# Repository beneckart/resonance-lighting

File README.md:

# Resonance Lighting

Power and lighting workstream for the **Resonance Tree** -- a bamboo art installation for Burning Man 2026 + 2027. This repo covers the roughly 130 solar/battery-powered, mesh-networked lighting fixtures in and around the tree -- four classes: hanging downlights, perimeter lights, trunk lights, and the central chandelier (canonical counts: the fleet table in `docs/block-diagram/SYSTEM.md`; current allocation: ADR 0032).

Sister tracks (not in this repo): bamboo structure (Bamboo Pure, Bali), structural engineering (Ed), parametric lighting design (Vishnu), project management (Elliot + Co-Work agent).

## Post-event storage and 2027 planning

Start with the [2026 postmortem and future-work index](docs/postmortem/README.md)
for the container-storage outcome, Oakland inventory, PROTECT investigation and
2027 hardware/tooling brainstorming. The
[storage and wake guide](docs/howto/FIXTURE_STORAGE_AND_WAKE.md) documents the
implemented USB/solar-wake ship mode, RESET-wake sleep, date picker and exact
retained firmware. These records supersede pre-event status where noted; the
2027 concepts remain discussion drafts.

## Who's working here

- **Ben Eckart** -- power systems, firmware, mesh networking. Owns `/firmware/` and `/hardware/`.
- **Steve Eckart** -- enclosure design, 3D printing, mechanical fit. Owns `/enclosure/`.

Both work with AI pair-programmers. Coordinate via `LOG.md`, `TODO.md`, and ADRs.
Firmware builders additionally use
[`docs/howto/FIRMWARE_ARTIFACT_HANDOFF.md`](docs/howto/FIRMWARE_ARTIFACT_HANDOFF.md)
so separate benches do not reuse revisions or silently flash each other's targets.

## What is the deliverable

Nominally 130 modular lighting fixtures in four classes -- 72 hanging downlights
in three rings of 24, 24 all-HEX perimeter lights on shepherd hooks, about 16 trunk
lights trending RGBW, and 18 mixed HEX/RGBW chandelier lights. The team intends to
build this full layout; fewer fixtures are a contingency for an unforeseen issue.
The archetype (hanging downlight) is:

- A bamboo lantern body, fabricated by Bamboo Pure in Bali.
- A solar "hat" enclosure that sits partially inside, partially over the bamboo top.
- A solar panel, rechargeable battery, controller board, LED module, sensors
  (accelerometer + downward ToF), and a 3D-printed patterned aperture / gobo.
- Firmware that supports autonomous ambient lighting, ESP-NOW state exchange, standard OTA maintenance updates, telemetry, and graceful low-power behavior.

The other classes are variants on the same electronics: perimeter lights use HEX and
face the ToF outward; trunk lights drop the gobo and are moving toward all RGBW while
a smaller lensed 3 W RGB module is tested for extra throw; chandelier lights live in
a carpenter-built box, likely on 6 Ah cells with USB-C top-ups. All share one firmware
image.

Steve's NeoHex Magic Wand is a separate one-off fleet peer, not a fifth
production class. Its PowerFeather identity is permanently `F40344` /
`68:EE:8F:F4:03:44`, its registry role is `magic_wand`, and batch OTA tooling
requires a dedicated single-target acknowledgement before it will touch that
MAC (ADR 0050). See `docs/projects/NeoHex-Magic-Wand/README.md`.

## Current architecture direction

**PowerFeather V2 (ESP32-S3) is the confirmed reference** for the controller / solar-and-battery manager / telemetry, after 5-board feasibility testing (ADR 0021): ESP-NOW mesh at scale, battery-only no-touch OTA + A/B rollback, and the solar charge path are all validated on hardware. Chemistry is **LiFePO4** (ADR 0002); batteries are two-tier since 2026-07-24 (ADR 0025): 33140 15 Ah in the large hats (downlights; qualification pending) and the fullbattery 32700 6 Ah, qualified n=2, in the small hats.

**The production path is decided: COTS PowerFeather V2, with a nominal 130-fixture
deployment (ADRs 0024 and 0032).**
158 boards are bought (68 received + 90 ordered 2026-07-09; ledger: `ops/PROCUREMENT.md`).
The custom PowerFeather-derived PCBA (ESP32-S3-WROOM module, BQ25628E-class charger,
MAX17260-class gauge, buck-boost 3.3 V rail, switchable rails, keyed connectors) is
the 2027 option, carrying the ADR 0028 bus-integrity rules.

The **LED axis is a mixed fleet by optical role** (ADR 0022): SK6812 "HEX"
direct-GPIO for close-range animation / ambient glow, and a 4 W RGBW point source for
long-throw crisp gobo projection. Both are driven **direct-GPIO off a free pin**, both
fed from the switchable 3V3 rail -- decided by instrumented A/B through
production-realistic cabling (ADR 0029 + 2026-07-11 amendment); the 4.2 V boost is
measured and shelved. The type mix by class is in the
SYSTEM.md fleet table (tentative until installation). The earlier Adafruit
IS31FL3741 13x9 STEMMA-QT matrix was **ruled out** (ADR 0018) -- it browns out the
board on battery under WiFi (shared charger/gauge I2C bus). The earlier COTS bake-off
candidates (FeatherS2 Neo, Atom Matrix, NeoHEX, DFR0559) served their purpose;
PowerFeather V2 won.

**Sensors and class identity** (ADRs 0027, 0034, 0041, 0067): every downlight
carries an MSA311 accelerometer + downward TMF8820-mini multizone ToF; perimeter
lights carry an outward VL53L5CX; trunk/uplights normally carry only MSA311;
chandelier lights carry no class sensors. Auto-classification is ordered ToF then
MSA311 at `0x62`, with a sensorless uplight fallback for the already-installed
2026 fleet. Remembered downlight/perimeter classes survive a missing ToF. Future
chandelier PowerFeathers are rostered by exact MAC and persist `class_ovr=4`
before installation. BMP581 is non-classifying environmental telemetry on the
outer 24 downlights. Fused IMUs were rejected (per-device calibration does not
scale to the fleet). The **noisemaker**
is decided (ADR 0030/0071): a solenoid mallet physically strikes an installed
finger cymbal on each canopy bamboo assembly -- daytime
solar-surplus percussion; the speaker-synth path was abandoned once the strikes
proved out.

**Production show timing is scheduled** (ADR 0031): four purchased SAM-M8Q modules
are the initial GPS/GNSS soft anchors for absolute UTC, and four purchased Adafruit
DS3231 modules are the initial battery-backed RTC holdover anchors. ESP-NOW distributes
time quality to the rest of the fleet, so all roughly 130 fixtures do not need RTCs.
Panel/lux dusk inference remains useful bench telemetry but is not the production show
clock.

**Performance audio has a dedicated optional publisher** (ADR 0035): a received
PUCA DSP Original Edition in its Eurorack expansion, paired with a RODE VideoMic
NTG, will analyze one clean audio source and publish directed show frames over
ESP-NOW. The already-proven CoreS3 + Module Audio path remains the independent
fallback. PUCA hardware is on hand; its development firmware now passes the
powered-Pod20 codec/stereo/control/radio/full-census baseline with locked
standalone HEARTBEAT startup. The performer's exact waveform, visible fixture
fidelity/fallback, and field validation remain pending. See
`hardware/puca-audio-bridge/README.md`.

**The camp network is pinned to the mesh channel** (ADR 0036). The ESP32-S3 has
one 2.4 GHz radio, so WiFi STA and ESP-NOW must share a channel, and in STA mode
the access point picks it. Every bridge so far dodges this by staying
unassociated; any device that wants the mesh and the internet at once cannot.
The camp AP (Starlink in bypass mode -> GL.iNet Beryl AX) therefore serves a
dedicated 2.4 GHz SSID fixed to channel 11, and any device that associates while
using ESP-NOW must verify the channel and drop WiFi rather than lose the mesh.
Router ordered, not yet configured; runbook in `docs/howto/CAMP_NETWORK_SETUP.md`.
Fixture maintenance images may carry two gitignored site credential profiles
and select the strongest visible known AP (ADR 0066). Ordinary fixture COMMS
never associates with either network, and no credential value enters git.
The first simultaneous mesh-plus-internet consumer is now **Resonance Bridge OS**
on the LilyGO T-Deck Plus. Hardware is on hand and M0-M4 plus the first M5 apps
are implemented and hardware-verified (ADRs 0047 and 0048). The channel guard
and WiFi/mesh coexistence passed on the house channel-11 network; Beryl field
configuration and validation remain open. The current app order is in
`firmware/tdeck_bridge/APP_ROADMAP.md`; CA Studio remains Greenberg-Hastings,
while the separate Contagion app owns Color Virus and Epidemic (ADR 0055).

The old custom-board target of ESP32-C3-MINI-1 + CN3058 + AP2112K + direct-from-battery WS2812B has been superseded by later ADRs.

## Goals

- **Fungible:** any unit replaces any other with no per-device configuration.
- **Fully wireless:** no data lines, no power lines, no fixed topology. ESP-NOW is for lightweight state/control packets, not firmware-image transfer.
- **Standard OTA only:** OTA updates use normal ESP32 OTA mechanisms in a deliberate maintenance mode. No custom mesh-gossiped firmware images.
- **Durable infrastructure:** fixtures are reused in 2026 and 2027.
- **Low per-fixture operations:** no skilled repetitive work at fleet scale. Small, deliberate soldering such as a solar pigtail can be acceptable; hand-soldering rows of headers or hand-crimping harnesses is not.
- **Telemetry:** power, solar, battery, temperature, and failure data should inform BM 2027 design decisions.
- **Beautiful:** default center-source gobo projection plus optional multi-LED chromatic/animation modes.

## Repo layout

```
.
|-- README.md
|-- LOG.md
|-- TODO.md
|-- BACKGROUND.md
|-- ROADMAP.md
|-- AGENTS.md
|-- hardware/
|   |-- atopile/
|   |-- led-adapter/       NeoHEX passive adapter Rev A (KiCad + PCBWay packet)
|   |-- puca-audio-bridge/ Received performance-audio source + bring-up record
|   `-- references/
|-- enclosure/             README only so far; CAD lives with Steve
|-- firmware/
|   |-- ARCHITECTURE.md    target production architecture
|   |-- README.md          index of the working bench sketches
|   |-- POWERFEATHER_NOTES.md
|   |-- powerfeather_solar_guard.h
|   `-- <app>/             bench sketches (net_bench, power_bench, led_studio, ...)
|-- docs/
|   |-- block-diagram/     SYSTEM.md -- canonical architecture + fleet table
|   |-- decisions/         ADRs 0001-0040
|   |-- howto/             task-oriented bench and operations guides
|   |-- research/
|   `-- tests/
`-- ops/
    |-- bom.md             fleet BOM + spares math
    |-- PROCUREMENT.md     orders ledger + timeline
    `-- bench/             bench tooling + JSONL data
```

## Read order for agents and humans

1. `README.md`
2. `LOG.md`
3. `TODO.md`
4. `BACKGROUND.md`
5. `docs/decisions/` -- especially ADRs 0010 onward
6. `docs/research/COTS_SURVEY_2026-05-10.md`
7. `docs/research/POWERFEATHER_V1_V2_SCHEMATIC_NOTES_2026-05-10.md`
8. `docs/tests/COTS_BENCH_TEST_PLAN_2026-05-10.md`

## How-to guides

- [`docs/howto/BRIDGE_OS_FIELD_MANUAL.md`](docs/howto/BRIDGE_OS_FIELD_MANUAL.md) --
  friendly illustrated field/IT manual for T-Deck Bridge OS, the CoreS3
  dashboard and audio modes, and the still-pending PUCA performance bridge.
- [`docs/howto/FIRMWARE_ARTIFACT_HANDOFF.md`](docs/howto/FIRMWARE_ARTIFACT_HANDOFF.md) --
  collision-proof firmware revision/manifest rules, explicit target handoff,
  fresh-evidence OTA completion, and USB boot-salute semantics for shared benches.
- [`docs/howto/CORES3_AUDIO_REACTIVE.md`](docs/howto/CORES3_AUDIO_REACTIVE.md) --
  connect and tune the Rode VideoMic NTG, read the CoreS3 envelope/FFT
  spectrogram and band modes, run the sound-reactive bench, and troubleshoot the
  safe fallback path.
- [`docs/howto/CAMP_NETWORK_SETUP.md`](docs/howto/CAMP_NETWORK_SETUP.md) --
  stand up Starlink + the Beryl AX travel router with the 2.4 GHz radio pinned to
  channel 11 so infrastructure WiFi and the ESP-NOW fleet can coexist on one
  radio. Home rehearsal, field checklist, and troubleshooting (ADR 0036).
## Fleet dashboard

CoreS3 Bridge OS now has a standalone touch Listener with a paged fleet-health
grid and fixture detail, so basic observation no longer needs a laptop. For the
complete host dashboard and telemetry logger, attach the same CoreS3 over USB.
The only Python dependency is `pyserial`; list the attached ports, then replace
`COM40` with the observed bridge port:

```sh
python -m pip install pyserial
python -m serial.tools.list_ports
python ops/bench/net_bench_dashboard.py --port COM40
```

The landing view is a compact grid of every ESP-NOW light. Battery fill and color,
charger-input activity, class-inferred source glyph, panel-suspect state, adaptive heartbeat freshness, and the
actual reported light output are readable without opening a table. The top bar is
the rendered LED color, independent from battery status. Callsigns from
`ops/fleet/callsigns.csv` lead in selected/detail and peer-list surfaces while
the exact short MAC remains visible and authoritative for state-changing work.
Reported fixture class
(normally from the Stemma probe, with an override available) sets the battery
glyph shape: circle for canopy/downlight, hexagon for
perimeter, triangle for trunk/uplight, and diamond for chandelier. Dense overview
tiles still use two MAC digits unless a collision needs `-1`, `-2`, and so on;
full callsigns would crowd that view. Select any light for exact
values; bench controls and the full historical telemetry console are preserved in
the collapsed `Detailed diagnostics` section. With `All` selected, `Strike all`
queues one addressed D7 pulse per fresh fixture after confirmation; disarmed boards
ignore it and the fixture's local power/mechanism gates remain authoritative. See
[`firmware/cores3_bridge/README.md`](firmware/cores3_bridge/README.md) for the
glyph contract and source-classification caveat.

Resonance Bridge OS embeds the same table in its Fleet and Health apps. Its
Claude tool surface accepts a callsign or six-hex short ID, resolves locally to
the MAC-derived target, and returns both in tool results. Fixture firmware and
the ESP-NOW packet contract do not carry callsigns.

For an explicit multi-fixture OTA, `ops/bench/fleet_dashboard_ota.py` accepts a
comma-separated short-MAC target list plus one already-built immutable binary.
It loads a job-scoped T-Deck roster, spans one selected sleep cadence, discovers
and identity-checks maintenance endpoints, positively freezes all gather traffic,
uploads in bounded parallel jobs, and requires fresh exact-revision evidence
beyond the A/B pending-verify gate. One exclusive-created ledger records every
target as verified, deferred, or failed. `--allow-partial-discovery` permits a
named sleeper cohort to proceed without missing targets; it never permits unnamed
discovery results or unsafe low-VBAT targets. See ADR 0062 and
`docs/howto/FLEET_OTA_10_MINUTE_RUNBOOK.md`.

## Status

As of 2026-08-06: **production is locked on COTS PowerFeather V2 with a current
130-fixture Nevada City layout in four classes (ADRs 0024 and 0032), and the buy is
essentially complete** -- boards, two battery
tiers, panels, LEDs, sensors, cabling, USB-C rescue ports, solarnoid hardware, and 172
Polycase enclosures are ordered or received (about $25.2k committed; ledger in
`ops/PROCUREMENT.md`). The qualified 32700 6 Ah cell remains the small-hat/chandelier
battery while 130 newly bought 33140 15 Ah cells are pending qualification for large
hats (ADR 0025). Panels are selected and outdoor-measured (ADR 0026); sensors are
allocated by class (ADR 0027); both LED roles are on the switchable 3V3 rail after
instrumented A/B (ADR 0029); the solarnoid is the selected noisemaker for large-hat
downlights (ADR 0030); and deterministic scheduled shows from sparse GPS/RTC anchors
are the production timing direction (ADR 0031).

Remaining gates during Nevada City assembly: the bottom-up nightly energy budget by
role, 33140 qualification and thresholds, trunk-light LED/power/mounting integration
(including the lensed 3 W RGB trial), hat thermal/RF proof on the Polycase boxes, the ADR 0023 state
machine in production firmware, solarnoid part/mounting details, and qualification of
the four SAM-M8Q GPS plus four DS3231 RTC timing anchors including invalid-time
behavior. Treat LFP SOC as advisory until the gauge learns; use coulomb counting and
voltage/current guardrails. See `LOG.md` and `TODO.md` for the live state.

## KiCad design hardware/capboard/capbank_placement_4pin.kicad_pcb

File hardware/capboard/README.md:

# Solarnoid cap-bank board — v2.0

> **CRITICAL -- fabricated v2.0 receiver supply is unsafe (2026-08-09).** Do
> not populate RECVR or plug in another RX480E. U1 is a Holtek HT7550-1, whose
> SOT-89 pins are 1=GND, 2=VIN, 3=VOUT, but the ordered board assigns pin 2 to
> P5V and pin 3 to the approximately 12 V VBOOST rail. This reverse-powers the
> regulator and can expose the nominal receiver `+V` pin to approximately boost
> voltage; `+V`-to-`G` measured 11.76 V on the first board. Two receivers
> emitted smoke during first bring-up. Keep RECVR empty
> until a measured ECO is qualified; the PowerFeather USER button and ESP-NOW
> command remain the safe trigger paths.

## Deployed rev-1 boards with the external boost cable

The 24 BMP-equipped outer-ring downlights use fabricated **rev-1 capboards**, not
the unsafe rev-2 receiver circuit described above. Their retrofit cable splices
an external approximately 12 V boost into the capboard input `VDC`/`GND`, so the
rev-1 bank, driver feed, and regulator input see the boosted voltage.

Rev 1 uses an AMS1117-5.0 with the correct SOT-223 mapping: pin 1 GND, pin 2/tab
5 V output, pin 3 boosted input. It is a linear regulator, not a buck converter;
at the RX480E's small load it drops approximately 12 V to 5 V and dissipates the
voltage difference as heat. Ben reports the populated rev-1 433 MHz receiver
paths operating normally on the boosted assemblies. This is consistent with the
rev-1 circuit and does not clear rev 2: rev 2 changed to an HT7550-1 with a
different pinout but retained the old net assignment, reverse-powering U1 and
putting 11.76 V on the nominal receiver rail. Before lid closure, spot-measure a
representative rev-1 receiver rail near 5 V and confirm U1 stays cool during an
extended powered test.

Strike-drive board for the bamboo-lantern noisemakers. Sits between the solar
panel and the Adafruit 5648 MOSFET driver: takes raw panel voltage in, **boosts
it to ~12 V**, buffers it in a 3 × 22,000 µF bank, and hands that to the
solenoid driver. Force on a reluctance actuator goes as V²/R, so the boost is
worth roughly **4× the strike energy** of the original 6 V design.

100 × 40 mm, 2 layer. **Ordered 2026-08-03: 10 panels of 6×2 = 120 boards.**

## Signal chain

```
panel ──> PANEL ──> MT3608 boost (~12.07 V) ──> 3× 22,000 µF ──> DRIVER ──> 5648 ──> solenoid
                                                     │
PowerFeather D7 ────────── (passes straight through) ┘
```

- **PANEL** and **DRIVER** are *not* the same net. PANEL carries raw panel
  volts (4.6–5.9 V); DRIVER carries the boosted rail. Swapping them is not
  destructive but gives weak knocks.
- **D7** is the ESP32 gate line; it passes through untouched on the back layer.

## Ports (bottom edge, left to right)

| Ref | Connector | Pinout |
|---|---|---|
| PANEL | JST XH 4p right-angle SMT | D7 · VDC · GND · GND |
| RECVR | 1×7 0.1" SMD socket | RX480E dock — G·5V·D0·D1·D2·D3·VT (**unpopulated**, see below) |
| TELE | JST XH 2p vertical THT | VSNS → A4 · BOOST_EN → A5 |
| DRIVER | JST XH 4p right-angle SMT | D7 · VBOOST · GND · GND |

Pin 4 on PANEL/DRIVER is a **second ground** — on DRIVER that splits the ~3 A
strike return across two contacts, which matters since XH is a 3 A series.

The 2-pin TELE is physically incompatible with the 4-pin power ports, so the
two cannot be cross-plugged. Reversing the TELE cable is harmless (both lines
are ADC-capable; firmware can tell them apart).

## Subsystems

- **Boost** — MT3608, 22 µH/2.4 A shielded inductor, SS34. Feedback 130 k/6.8 k
  → 0.6 × (1 + 130/6.8) ≈ **12.07 V**. R12 (THT, DNP) parallels the lower leg to
  trim *upward*; watch the 16 V caps if you push far. **JP1** (DNP) bypasses the
  boost entirely — close it and the board reverts to v1.0 behaviour.
- **EN** — 47 k/47 k divider off VDCIN holds EN at ~VIN/2, so the boost
  **self-enables with nothing plugged in**, and a GPIO on TELE pin 2 can pull it
  low. The GPIO never sees more than ~3.0 V.
- **One-shot button (SW1)** — VDC→SW1→470R→10 µF→D7, zener-clamped. One ~40 ms
  pulse per press; the series cap blocks DC, so a stuck button *cannot* park the
  coil energised (a lit panel would otherwise sustain 2.5–4 W into the coil).
  C1B (THT, DNP) parallels C1 to lengthen the pulse. Fixture firmware
  `2026-08-09.2` and later detects the released-to-HIGH edge and takes over D7
  for its independently bounded 40 ms pulse; the hardware one-shot remains the
  initiator and DC/stuck-input bound.
- **Receiver rail (U1) -- AS-FAB UNSAFE:** the intended HT7550-1 5 V rail has
  VIN and VOUT reversed on fabricated v2.0; see the critical warning above.
  Replacing the AMS1117 was intended to remove its 5-10 mA idle draw, but the
  pinout changed with the part and was not carried into the footprint nets.
- **Telemetry** — VSNS = VBOOST × 6.8/53.8 → A4; 47 k/6.8 k with 1 nF gives
  ~27 kHz of bandwidth, enough to actually capture the 25 ms droop transient.

## Fab package (upload these three)

| File | |
|---|---|
| `build/capbank_gerbers_v2.0_4pin.zip` | gerbers + drills |
| `capbank_cpl_4pin.csv` | 23 SMT parts |
| `capbank_bom_smt_4pin.csv` | every line carries an LCSC part number |

Settings: 2-layer FR-4, 100 × 40 mm, green/white, HASL leaded, 1.6 mm, 1 oz,
tented vias, remove mark, **SMT top side only**.

**RECVR is deliberately unpopulated** — no SMD female header has stock anywhere.
The RX dock is optional per node (production triggering is the ESP-NOW clicker),
so its pads stay bare and a socket can be hand-fitted on whichever boards ever
get a 433 MHz receiver.

No verified 12 V receiver has the RX480E 1x7 drop-in footprint. If local RF is
still wanted on fabricated v2.0, use a compact wide-input 433 MHz receiver with
an isolated dry-contact output on a short five-wire harness. The leading bench
candidate is QIACHIP
[KR1201MINI2-V05B](https://qiachip.com/products/kr1201mini2-v05b-mini-relay-remote-control-dc3v-5v-9v-12v-24v-all-compatible-dry-contact-2a-load-current-rf-433mhz-remote-control-switch)
(3.7-24 V input, 31 x 14 x 7 mm,
momentary/toggle/latching modes). Wire receiver power `+` to true VBOOST and `-`
to GND at DRIVER; wire relay COM to raw VDCIN at PANEL and relay NO to the
RECVR D0/BTNP pad so the contact exactly imitates SW1 upstream of R7 and the
one-shot. Leave NC unused. Do not power it from the damaged RECVR `5V` pad,
despite the 11.76 V unloaded reading, and never route 12 V directly into D0 or
D7. Qualify current draw, remote compatibility, momentary setup, strike-rail
droop, and sleep energy before fleet use.

**Hand-soldered in Nevada City — 8 joints/board:** the 3 electrolytics and the
2-pin TELE. C1B, R12, JP1 are DNP options.

Cap voltage ratings are deliberate and annotated in the BOM: C1/C7/C8 never see
more than ~6 V so 16 V is ample, **C9 is the only part on the 12 V rail and must
stay 25 V.** Letting the picker default to 50 V parts cost $131 on the first quote.

## Workflow — placement is Ben's, routing is scripted

Positions and silkscreen are hand-placed in KiCad and are **authoritative**.
`route_capboard.py` / `route_4pin.py` load the placement file and add *only*
tracks, vias and the ground pour, so routing is reproducible after any
re-arrangement and never fights the layout.

```bash
python3 route_4pin.py                                    # 4-pin (production)
kicad-cli pcb drc --refill-zones --save-board --severity-error \
    --exit-code-violations -o build/drc.rpt build/capbank_4pin.kicad_pcb
```

**Edit `capbank_placement_4pin.kicad_pcb`, never `build/capbank_4pin.kicad_pcb`** —
the latter is regenerated and your changes would be lost. If you do edit the
build output by accident, its positions can be synced back into the placement
file (that is how the v2.0 PANEL/TELE nudges were recovered).

| File | Role |
|---|---|
| `capbank_placement_4pin.kicad_pcb` | **source of truth** — placement + silkscreen |
| `route_4pin.py` | adds copper; regenerates `build/capbank_4pin.kicad_pcb` |
| `capbank_4pin_ben.kicad_pcb` | snapshot of the hand-edited board, for reference |
| `capbank_placement_ben.kicad_pcb` + `route_capboard.py` | 3-pin variant (S3B is out of stock; kept as fallback) |
| `generate_capboard_v10.py.bak` | the v1.0 generator, the board that was actually fabbed first |

## CAD for the plate

`cad/` holds v2.0 STEP/DXF/VRML exports — see `cad/README.md`. Mounting holes
are unchanged from v1.0 at **(3.2, 3.2), (84.8, 3.2), (84.8, 36.8), (3.2, 36.8)**,
so existing plates fit; the board simply overhangs 15 mm past the right pair.
3.2 mm holes take M2.5 or M3.

## Before the next order

- Correct U1 to HT7550-1 pins 1=GND, 2=VBOOST/VIN, 3=P5V/VOUT and create a new
  board revision; do not silently regenerate this as v2.0. Before release,
  measure the receiver rail unloaded and with a current-limited dummy load.
- Verify the RX480E module pin order against physical parts if RECVR is ever
  populated (assumed GND · +V · D0 · D1 · D2 · D3 · VT).
- Cables are crimped from raw leads: press them **straight, never mirrored** —
  a mirrored cable swaps D7 and GND and puts the bank across the gate line.

## 2026-10-11 -- Bodhi Hive VBAT-fed chime experiment

Ben fitted a PowerFeather header across `VBAT | EN | VS | D13` and moved the
v2 capboard's input supply from VDC to VBAT. He confirmed the LFP is installed
and the capboard's old solar/VDC feed is disconnected. USB was connected for
service. The intent is to keep the existing D7 trigger and strike from stored
battery energy without requiring sunlight; this is an experiment, not a
fleet-qualified power-source change.

Intended connectivity (retain the existing common-ground and D7 harness):

```
PowerFeather VBAT -> capboard PANEL VDC/VDCIN -> onboard boost -> cap bank
PowerFeather GND  -> capboard PANEL GND      -> driver/coil return
PowerFeather D7   -> capboard PANEL D7       -> driver trigger
```

The four new header positions are not the capboard PANEL connector pinout.
Use only the intended VBAT takeoff; EN, VS and D13 are separate nets. VS is
external-input-derived (USB/VDC), not the battery output. PowerFeather EN is
FeatherWing control, not the capboard TELE BOOST_EN. D13 is GPIO11; the strike
remains D7/GPIO37. The manufacturer specifies the MT3608 for 2-24 V input,
so LFP input is within the IC's stated input range; this does not qualify this
assembled board's startup, recharge current or battery ride-through.

Current fixture source already permits deliberate serial/operator strikes
without a daylight/solar gate (ADR 0065). It retains arm, pulse/rest, durable
load-marker and failsafe requirements. Sleeping receivers still cannot hear
mesh commands, and automatic chimes follow separate policy. Read the installed
artifact and exact MAC before using `K<short-MAC>:40` for one bounded USB pulse.
No strike or flash was performed during the initial inspection because Windows
reported no serial ports, including unrestricted enumeration.

Ben subsequently reported a correct strike from the PowerFeather USER button
during USB/bootloader diagnosis, with USB connected. This confirms a local
button-triggered strike in the modified setup, not battery-only refill or
USB/ROM communication. Ben confirmed it struck on the initial USER press,
before RESET, so this is not evidence of application execution after attempted
ROM entry.

Bypassing the enclosure USB extension subsequently restored direct USB on
COM14 and identified the fixture as Ness, `9F2738` (`D8:85:AC:9F:27:38`). ROM
communication passed. Physical RESET then booted the existing
`fx-260912-f951ae9-b` image with the solenoid enabled. USB supply was good,
charging enabled after startup qualification, and the gauge reported positive
charge current. The fixture was not in PROTECT; it recovered from DIM to FULL
allowance after about 65 seconds. No firmware update or manual protection
clear was needed. The enclosure USB extension path still requires repair or
qualification.

Basic battery-only test then passed on Ness: Ben disconnected USB, retained
the LFP, and reported two normal USER chimes ten seconds apart. After direct
USB reconnection, the strike counter had advanced from 0 to 2, last pulse was
40 ms, blocks/failsafes remained zero, and uptime was continuous across the
test. The gate was off afterward and USB charging resumed positive gauge
current. This does not measure capbank refill or long-term battery drain.

Later on October 11, a controlled extension A/B again produced Windows Code 43
before/after physical RESET, with the board-end USB-C plug rotated 180 degrees,
and after a fresh laptop reconnect. Bypassing only the extension with the same
laptop cable immediately restored COM14 and live application telemetry at
106552 ms uptime. The extension/connector path is therefore a real problem in
this setup; ordinary deep-sleep disconnects are a separate effect. Exact cable
versus contact failure is still unisolated.

Ben then requested a classic seven-hit door knock. Direct USB commands
`K9F2738:40` at offsets 0, 0.5, 0.75, 1.0, 1.5, 2.5 and 3.0 seconds produced
seven firmware-confirmed strikes, counter 0 -> 7, zero blocks/failsafes, gate
off afterward and continuous uptime. Ben confirmed the full cadence sounded
good. This was USB-powered, not a battery-only rapid-refill test. Evidence is in
the 20261012T004337Z and 20261012T004614Z traces under
`ops/bench/data/Bodhi Hive/` (UTC date October 12, local date October 11).

Ben subsequently connected a replacement enclosure extension. Three fresh
COM14 telemetry replies confirmed continuous Ness uptime, good supply around
4.64 V, charging enabled, +173 to +270 mA gauge current and no BQ fault.
The replacement passes this basic data/charging check; the original extension
is the suspect assembly. No reset or additional strike was used for this check.

A requested replay through the replacement extension also registered all seven
strikes (counter 7 -> 14), but Ben heard clumping in the opening phrase. The
host emitted separate immediate commands with roughly 30 ms interval error;
some return reports were buffered together in both recordings. This does not
isolate USB transport, firmware scheduling or mechanics as the audible cause.
Accurate rhythm needs actual onset measurements and preferably a locally
timed phrase. Seven accepted strikes alone are not a timing qualification.

Qualification still needed: check approximately 12 V at the charged driver
rail and measure refill/repeated-duty behavior without USB or solar assistance
while retaining the LFP. Measure standby and recharge current externally.
The boost self-enables through its 47k/47k EN divider, and current firmware does
not manage TELE BOOST_EN; cutting the LED rail does not disconnect this load.
The prior bench notes identify the VBAT header load as bypassing the gauge
shunt, so reported battery current/SOC must not be the only energy evidence.
Battery drain and a suitable low-battery cutoff remain open before unattended
use. Keep the fabricated v2 RECVR socket empty because of its known U1 pinout
fault; changing input supply does not repair that circuit.

References: [PowerFeather pins and power](https://docs.powerfeather.dev/),
[MT3608 manufacturer](https://www.aerosemi.com/forum.php?mod=viewthread&tid=32),
`../../firmware/POWERFEATHER_NOTES.md`, and ADR 0065.

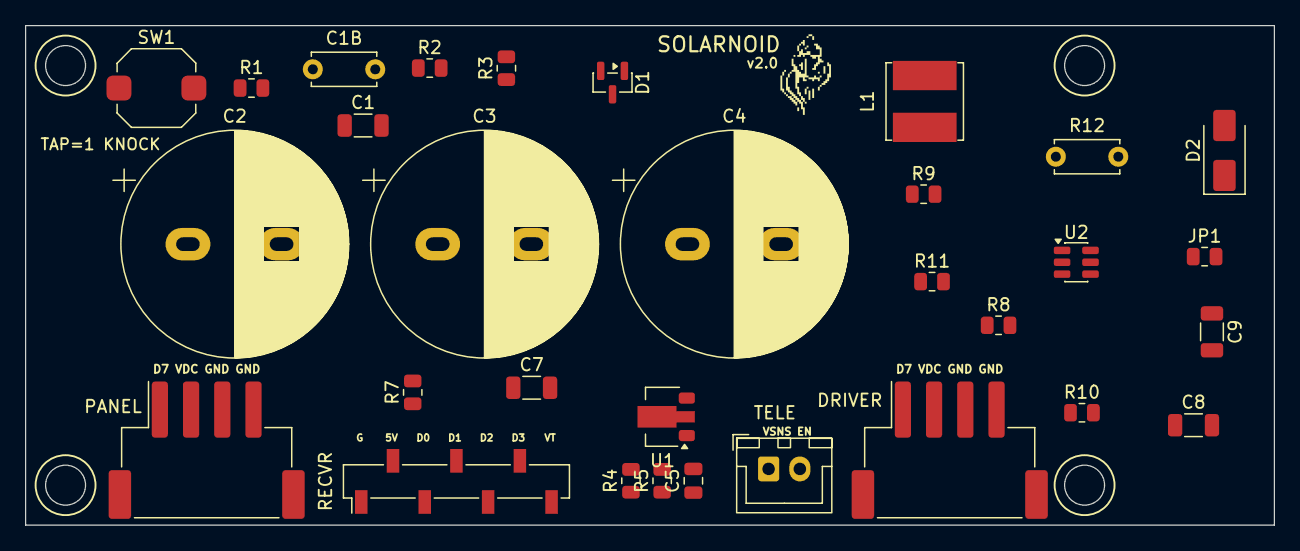
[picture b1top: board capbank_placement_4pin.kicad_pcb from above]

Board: 2 copper layers, 100.0 x 40.0 mm, 31 parts (0 on the bottom side), 12 nets, no tracks yet.

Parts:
C1, C7: 10uF X7R 16V; C_1206_3216Metric
C1B: DNP; C_Disc_D5.0mm_W2.5mm_P5.00mm
C2, C3, C4: 22000u 16V; CP_Radial_D18.0mm_P7.50mm
C5: 1n; C_0805_2012Metric
C8: 22uF 16V; C_1206_3216Metric
C9: 10uF 25V; C_1206_3216Metric
D1: BZX84C3V3; SOT-23
D2: SS34; D_SMA
DRIVER: XH 4p SMT (pin4=GND); JST_XH_S4B-XH-SM4-TB_1x04-1MP_P2.50mm_Horizontal
JP1: BYPASS DNP; R_0805_2012Metric
L1: 22uH 2.4A; L_Bourns_SRN6045TA
PANEL: XH 4p SMT (pin4=GND); JST_XH_S4B-XH-SM4-TB_1x04-1MP_P2.50mm_Horizontal
R1: 470R; R_0805_2012Metric
R2: 330k; R_0805_2012Metric
R3: 10k; R_0805_2012Metric
R4, R10, R11: 47k; R_0805_2012Metric
R5, R9: 6.8k; R_0805_2012Metric
R7: 1k; R_0805_2012Metric
R8: 130k; R_0805_2012Metric
R12: DNP TRIM; C_Disc_D5.0mm_W2.5mm_P5.00mm
RECVR: RX480E DOCK; PinSocket_1x07_P2.54mm_Vertical_SMD_Pin1Left
SW1: SW_Push_1TS009xxxx-xxxx-xxxx_6x6x5mm
TELE: VSNS/EN; JST_XH_B2B-XH-A_1x02_P2.50mm_Vertical
U1: HT7550-1; SOT-89-3
U2: MT3608; SOT-23-6

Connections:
BTNP: R7.1, RECVR.3
D7: C1.2, C1B.2, D1.3, DRIVER.1, PANEL.1, R2.2, R3.1
EN: R10.1, R11.2, TELE.2, U2.4
FB: R8.1, R9.2, R12.1, U2.3
GND: C2.2, C3.2, C4.2, C5.1, C7.1, C8.2, C9.2, D1.1, DRIVER.3, DRIVER.4, PANEL.3, PANEL.4, R3.2, R5.1, R9.1, R11.1, R12.2, RECVR.1, U1.1, U2.2
NETA: R1.1, R7.2, SW1.2
NETB: C1.1, C1B.1, R1.2, R2.1
P5V: C7.2, RECVR.2, U1.2
SW: D2.2, L1.2, U2.1, U2.6
VBOOST: C2.1, C3.1, C4.1, C9.1, D2.1, DRIVER.2, JP1.2, R4.2, R8.2, U1.3
VDCIN: C8.1, JP1.1, L1.1, PANEL.2, R10.2, SW1.1, U2.5
VSNS: C5.2, R4.1, R5.2, TELE.1

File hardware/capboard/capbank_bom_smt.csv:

Comment,Designator,Footprint,JLCPCB Part #
470R 0805 1%,R1,R0805,C17710
330k 0805 1%,R2,R0805,C17629
10k 0805 1%,R3,R0805,C17414
47k 0805 1%,"R4,R10,R11",R0805,C17713
6.8k 0805 1%,"R5,R9",R0805,C17772
1k 0805 1%,R7,R0805,C17513
130k 0805 1%,R8,R0805,C2933305
10uF 16V X7R 1206,"C1,C7",C1206,C342827
1nF 50V 0805,C5,C0805,C46653
22uF 16V X7R 1206,C8,C1206,C5252682
10uF 25V X7R 1206,C9,C1206,C6119987
BZX84C3V3 zener,D1,SOT-23,C19077467
SS34 schottky,D2,SMA/DO-214AC,C8678
HT7550-1 LDO,U1,SOT-89,C16106
MT3608 boost,U2,SOT-23-6,C84817
22uH 2.4A shielded,L1,SRN6045 6x6mm,C2849539
6x6 SMD tactile 2-pin,SW1,1TS009 6x6mm,C319428
JST S3B-XH-SM4-TB right-angle SMT 3p (OUT OF STOCK - see 4pin BOM),"PANEL,DRIVER",JST_XH_SM4_1x03_RA,

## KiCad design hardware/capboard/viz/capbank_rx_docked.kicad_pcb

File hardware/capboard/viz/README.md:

# Visualization boards (not fab artifacts)

`capbank_rx_docked.kicad_pcb` is the v1.0 cap-bank board with an RX480E-4
receiver module posed in the RECVR socket, for viewing in the KiCad 3D viewer.
It is **visualization only** — it never feeds gerbers, drills, placement, or
BOM, and the fab board (`../build/capbank.kicad_pcb`) carries no such model.

Rebuild it:

```bash
./fetch_rx_model.sh                  # once: pulls radio-receiver.step
python3 generate_capboard.py         # regenerates the fab board
python3 make_rx_viz.py               # writes viz/capbank_rx_docked.kicad_pcb
```

## About the 3D model

`radio-receiver.step` comes from https://github.com/besi/kicad-radio-receiver
(3D model credited there to Alejandro Hurtado via GrabCAD). That project ships
**no license file**, so the model is deliberately not committed here — the
fetch script pulls it on demand. It represents the RX480E-4 family rather than
any specific vendor's board, so treat it as indicative, not dimensional truth.

## Fitted pose

`rot (90, 180, 90)`, `offset (-4.1, -12.595, 14.64)`, fitted by eye against the
real part. RECVR sits at 90°, so the offset axes are rotated relative to the
board: `offset.x` moves along board −Y (≈4.1 mm of standoff for the right-angle
pins' horizontal run before they turn down), `offset.y` along board −X (2.54 mm
= one pin pitch), `offset.z` straight up (socket body + header thickness).

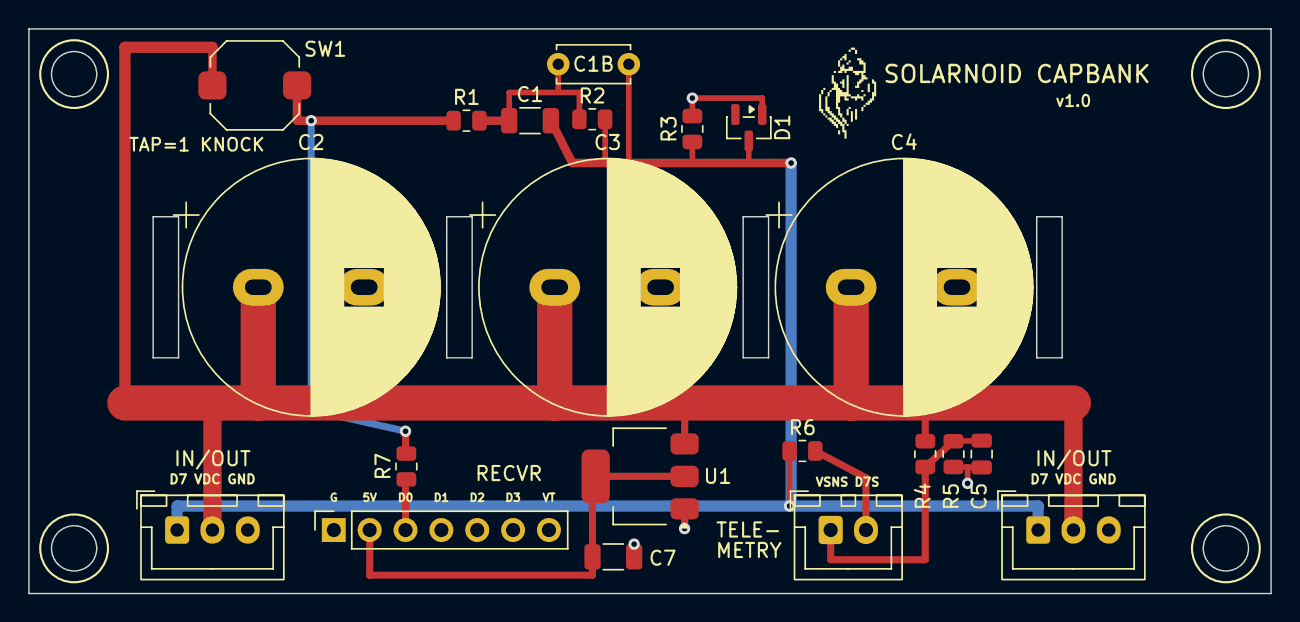
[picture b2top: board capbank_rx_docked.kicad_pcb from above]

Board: 2 copper layers, 88.0 x 40.0 mm, 21 parts (0 on the bottom side), 9 nets.

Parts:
C1, C7: 10uF X7R 16V; C_1206_3216Metric
C1B: DNP; C_Disc_D5.0mm_W2.5mm_P5.00mm
C2, C3, C4: 22000u 16V; CP_Radial_D18.0mm_P7.50mm
C5: 100n; C_0805_2012Metric
D1: BZX84C3V3; SOT-23
IN/OUT: JST_XH_B3B-XH-A_1x03_P2.50mm_Vertical
IN/OUT#2: JST_XH_B3B-XH-A_1x03_P2.50mm_Vertical
METRY: SENSE; JST_XH_B2B-XH-A_1x02_P2.50mm_Vertical
R1: 470R; R_0805_2012Metric
R2: 330k; R_0805_2012Metric
R3: 10k; R_0805_2012Metric
R4: 100k; R_0805_2012Metric
R5: 33k; R_0805_2012Metric
R6, R7: 1k; R_0805_2012Metric
RECVR: RX480E DOCK; PinSocket_1x07_P2.54mm_Vertical
SW1: SW_Push_1TS009xxxx-xxxx-xxxx_6x6x5mm
U1: AMS1117-5.0; SOT-223-3_TabPin2

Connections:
BTNP: R7.1, RECVR.3
D7: C1.2, C1B.2, D1.3, IN/OUT.1, IN/OUT#2.1, R2.2, R3.1, R6.1
D7S: METRY.2, R6.2
GND: C2.2, C3.2, C4.2, C5.1, C7.2, D1.1, IN/OUT.3, IN/OUT#2.3, R3.2, R5.1, RECVR.1, U1.1
NETA: R1.1, R7.2, SW1.2
NETB: C1.1, C1B.1, R1.2, R2.1
P5V: C7.1, RECVR.2, U1.2
VDC: C2.1, C3.1, C4.1, IN/OUT.2, IN/OUT#2.2, R4.2, SW1.1, U1.3
VSNS: C5.2, METRY.1, R4.1, R5.2

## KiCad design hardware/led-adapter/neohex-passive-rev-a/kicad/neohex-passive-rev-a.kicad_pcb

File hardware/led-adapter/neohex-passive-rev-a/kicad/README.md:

# KiCad Starter Project

Status: starter PCB layout, not order-ready.

Files:

- `neohex-passive-rev-a.kicad_pro` - KiCad 10 project file.
- `neohex-passive-rev-a.kicad_pcb` - routed starter PCB layout.
- `generate_starter_pcb.py` - reproducible generator for the starter board.
- `fp-lib-table` and `resonance.pretty/` - local footprint library for the
  M5Stack HY2.0-4P SMD candidate.

Important caveats:

- J1 uses the local `resonance:M5Stack_HY2.0-4P_SMD_A118` candidate footprint.
  It is intended to match M5Stack's A118 HY2.0-4P SMD connector, but still
  needs physical verification against the M5Stack NeoHEX/HEX cable before
  ordering boards.
- J2 uses stock `Connector_JST:JST_PH_S2B-PH-SM4-TB_1x02-1MP_P2.00mm_Horizontal`.
- J5 uses stock `Connector_JST:JST_SH_BM04B-SRSS-TB_1x04-1MP_P1.00mm_Vertical`
  as a fallback output for Adafruit 4528-style Grove-to-STEMMA-QT cables.
- Verify J1 cable orientation before ordering. The intended net order is
  `1 GND`, `2 VLED`, `3 DATA`, `4 NC`.
- Verify J5 cable orientation before ordering. The intended net order is
  `1 GND`, `2 VLED`, `3 NC`, `4 DATA`, matching the NeoHEX signal on the
  Grove yellow/SCL-position conductor.
- No schematic has been captured yet; the authoritative electrical intent is
  still the parent directory's `README.md` and `netlist.csv`.
- This first layout is intentionally roomy at 72 mm x 35 mm so the routing and
  connector intent are easy to inspect. Shrink only after the connector family
  and mounting approach are settled.
- 3D view caveat: J1 has no local STEP model yet, and the stock J2 footprint
  references a JST-PH-SM4 STEP model that is missing from the current KiCad
  package. J3/J4/J5 use stock JST-SH models and should appear in 3D view.

Validation commands:

```sh
python3 hardware/led-adapter/neohex-passive-rev-a/kicad/generate_starter_pcb.py
kicad-cli pcb drc --output /tmp/res-neohex-kicad/drc.rpt hardware/led-adapter/neohex-passive-rev-a/kicad/neohex-passive-rev-a.kicad_pcb
kicad-cli pcb export gerbers --output /tmp/res-neohex-kicad/gerbers hardware/led-adapter/neohex-passive-rev-a/kicad/neohex-passive-rev-a.kicad_pcb
kicad-cli pcb export drill --output /tmp/res-neohex-kicad/drill hardware/led-adapter/neohex-passive-rev-a/kicad/neohex-passive-rev-a.kicad_pcb
```

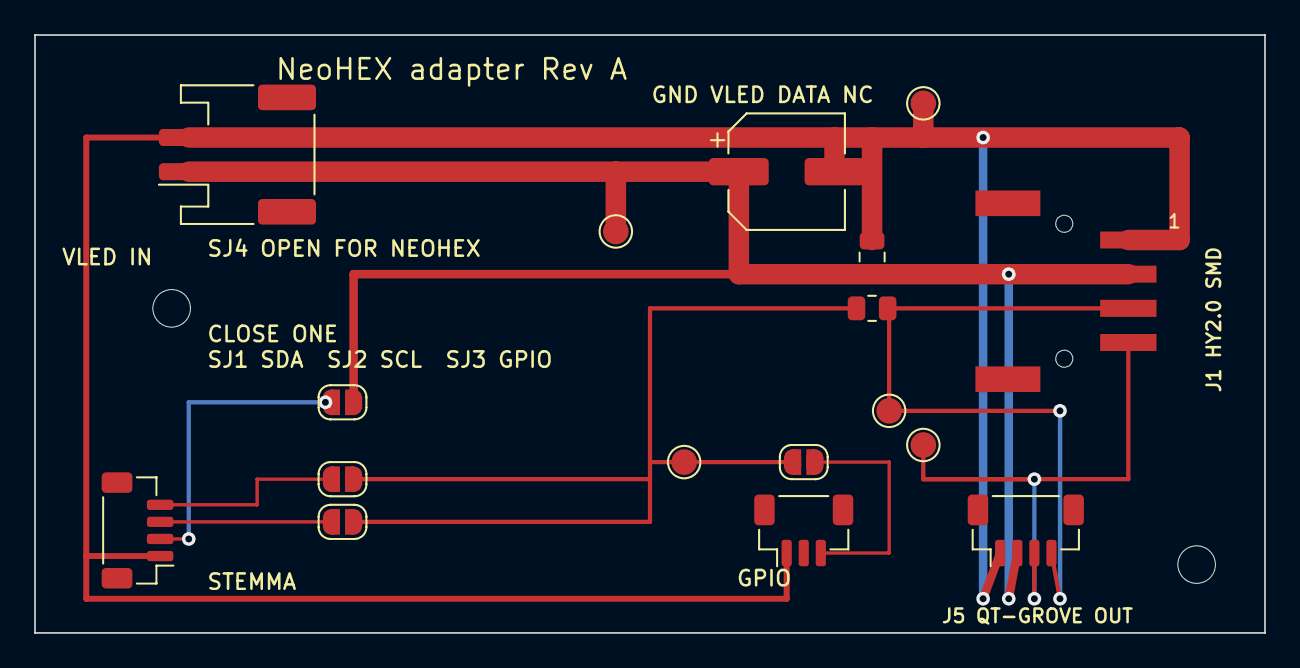
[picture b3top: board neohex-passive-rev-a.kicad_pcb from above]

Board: 2 copper layers, 72.0 x 35.0 mm, 19 parts (0 on the bottom side), 9 nets.

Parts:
C1: 0.1uF; C_0805_2012Metric
C2: 100-470uF_DNP; CP_Elec_6.3x5.4
H1, H2: M2; MountingHole_2.2mm_M2
J1: HY2.0_4P_SMD_OUT; M5Stack_HY2.0-4P_SMD_A118
J2: VLED_IN; JST_PH_S2B-PH-SM4-TB_1x02-1MP_P2.00mm_Horizontal
J3: STEMMA_DATA; JST_SH_BM04B-SRSS-TB_1x04-1MP_P1.00mm_Vertical
J4: GPIO_DATA; JST_SH_BM03B-SRSS-TB_1x03-1MP_P1.00mm_Vertical
J5: QT_GROVE_OUT; JST_SH_BM04B-SRSS-TB_1x04-1MP_P1.00mm_Vertical
R1: 330R; R_0805_2012Metric
SJ1, SJ2, SJ3, SJ4: OPEN; SolderJumper-2_P1.3mm_Open_RoundedPad1.0x1.5mm
TP1: VLED; TestPoint_Pad_D1.5mm
TP2: GND; TestPoint_Pad_D1.5mm
TP3: DATA_RAW; TestPoint_Pad_D1.5mm
TP4: DATA_OUT; TestPoint_Pad_D1.5mm
TP5: NC; TestPoint_Pad_D1.5mm

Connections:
DATA_OUT: J1.3, J5.4, R1.2, TP4.1
DATA_RAW: R1.1, SJ1.2, SJ2.2, SJ3.2, TP3.1
GND: C1.2, C2.2, J1.1, J2.2, J3.1, J4.1, J5.1, TP2.1
GPIO_DIN: J4.3, SJ3.1
NC_WHITE: J1.4, J5.3, TP5.1
STEMMA_SCL: J3.4, SJ2.1
STEMMA_SDA: J3.3, SJ1.1
STEMMA_VPLUS: J3.2, SJ4.1
VLED: C1.1, C2.1, J1.2, J2.1, J5.2, SJ4.2, TP1.1

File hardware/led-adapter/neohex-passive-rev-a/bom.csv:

Ref,Qty,Value,Package,Description,Assembly Notes
J1,1,,M5Stack A118 HY2.0-4P SMD candidate,HEX/NeoHEX output connector,Verify local footprint and cable pin order before ordering
J2,1,,JST_PH_S2B-PH-SM4-TB_1x02-1MP_P2.00mm_Horizontal,External LED power input,SMT JST-PH candidate; verify against chosen pre-crimped leads
J3,1,,JST_SH_BM04B-SRSS-TB_1x04-1MP_P1.00mm_Vertical,STEMMA/QT data input,Optional for STEMMA data variant
J4,1,,JST_SH_BM03B-SRSS-TB_1x03-1MP_P1.00mm_Vertical,Generic GPIO data input,Optional for generic GPIO variant
J5,1,,JST_SH_BM04B-SRSS-TB_1x04-1MP_P1.00mm_Vertical,HEX/NeoHEX fallback output,For Adafruit 4528-style Grove-to-STEMMA-QT cable; J5.4 is DATA
R1,1,330 ohm,R_0805_2012Metric,LED data series resistor,Place near J1
C1,1,0.1 uF,C_0805_2012Metric,VLED decoupling,Place near J1 VLED/GND
C2,1,100-470 uF >=6.3 V,CP_Elec_6.3x5.4,Optional VLED bulk capacitor,DNP if module/power path already has adequate bulk capacitance
SJ1,1,,2-pad solder jumper,Select STEMMA SDA as data,Close one of SJ1/SJ2/SJ3 only
SJ2,1,,2-pad solder jumper,Select STEMMA SCL as data,Close one of SJ1/SJ2/SJ3 only
SJ3,1,,2-pad solder jumper,Select generic GPIO as data,Close one of SJ1/SJ2/SJ3 only
SJ4,1,,2-pad solder jumper,Optional STEMMA V+ to VLED,Default open; silkscreen NO NEOHEX
TP1,1,VLED,1.5mm test pad,VLED test point,
TP2,1,GND,1.5mm test pad,GND test point,
TP3,1,DATA_RAW,1.5mm test pad,Pre-resistor data test point,
TP4,1,DATA_OUT,1.5mm test pad,Post-resistor data test point,
TP5,1,NC,1.5mm test pad,Grove white/NC test point,

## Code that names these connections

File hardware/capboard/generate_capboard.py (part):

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B2XH = "JST_XH_B2B-XH-A_1x02_P2.50mm_Vertical"

# ---- parameters -------------------------------------------------------------
PIN_ORDER = {"1": "D7", "2": "VDC", "3": "GND"}   # matches PowerFeather header
RX_ORDER = ["GND", "P5V", "BTNP", None, None, None, None]   # GND 5V D0 D1 D2 D3 VT
RX_LABELS = ["G", "5V", "D0", "D1", "D2", "D3", "VT"]
BOARD_W, BOARD_H = 100, 40
CAP_CENTERS = [20, 41, 62]
CAP_Y = 18.3
CAP_PITCH = 7.5
SPINE_Y = 26.5        # VBOOST spine (front)
D7_Y = 33.8           # D7 spine (back, under the connector row)
RAIL_X = 6.8          # VDC rail riser (clears the top-left mounting hole)
RAIL_Y = 1.3          # VDC rail to button cluster
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assign(jp1, {"1": "VDCIN", "2": "VBOOST"})

# ---- routing ----------------------------------------------------------------
# Layer lanes (front unless noted):  y=26.5 VBOOST spine | back y=28.0 EN |
# back y=29.5 VDCIN | y=30.75 SM4 signal pads | back y=33.8 D7 spine
j1d, j1v, j1g = pxy(j1, "1"), pxy(j1, "2"), pxy(j1, "3")
j2d, j2v, j2g = pxy(j2, "1"), pxy(j2, "2"), pxy(j2, "3")
VIA_Y = 32.0
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track(*jp1b_, 97.0, 17.0, 0.6, F, "VBOOST")
track(97.0, 17.0, 97.0, 22.0, 0.6, F, "VBOOST")

# --- VBOOST spine ---
track(97.0, 22.0, 97.0, SPINE_Y, 1.6, F, "VBOOST")
track(RAIL_X + 8, SPINE_Y, 97.0, SPINE_Y, 2.5, F, "VBOOST")
for cx in CAP_CENTERS:
    track(cx - CAP_PITCH / 2, CAP_Y, cx - CAP_PITCH / 2, SPINE_Y, 2.5, F, "VBOOST")
track(*j2v, j2v[0], SPINE_Y, 1.6, F, "VBOOST")
u1vin, u1gnd, u1out = pxy(u1, "3"), pxy(u1, "1"), pxy(u1, "2")
track(*u1vin, u1vin[0], SPINE_Y, 0.5, F, "VBOOST")
r4s, r4v = pxy(r4, "1"), pxy(r4, "2")
track(*r4v, r4v[0], SPINE_Y, 0.4, F, "VBOOST")

# --- VDCIN: PANEL -> left margin -> top rail (all front) ---
sw_vdc = pxy(sw1, "1")
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track(48.0, LANE_Y, 48.0, 24.0, 0.8, B, "D7")
track(48.0, 24.0, 40.0, D7_Y, 0.8, B, "D7")

# --- VSNS divider -> TELE pin 1 ---
r5g, r5s = pxy(r5, "1"), pxy(r5, "2")
c5g, c5s = pxy(c5, "1"), pxy(c5, "2")
track(*r4s, *r5s, 0.4, F, "VSNS")
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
